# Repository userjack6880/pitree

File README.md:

There's not much to say. This is a perl script that enables a raspberry pi to control a specific
hardware tree, files should be included with this script. The schematics and board layout are 
distributed under Creative Commons Attribution-ShareAlike 4.0 International. The software is
distributed under GNU General Public License v3.

You'll need a few perl modules to get this working.

- DateTime
- JSON
- Device::BCM2835
- Switch
- Data::Dumper
- LWP::UserAgent
- LWP::Protocol::https
- Time::HiRes qw(usleep)
- Curses
- Net::Ping

Have a Merry Christmas and a Happy New Year.

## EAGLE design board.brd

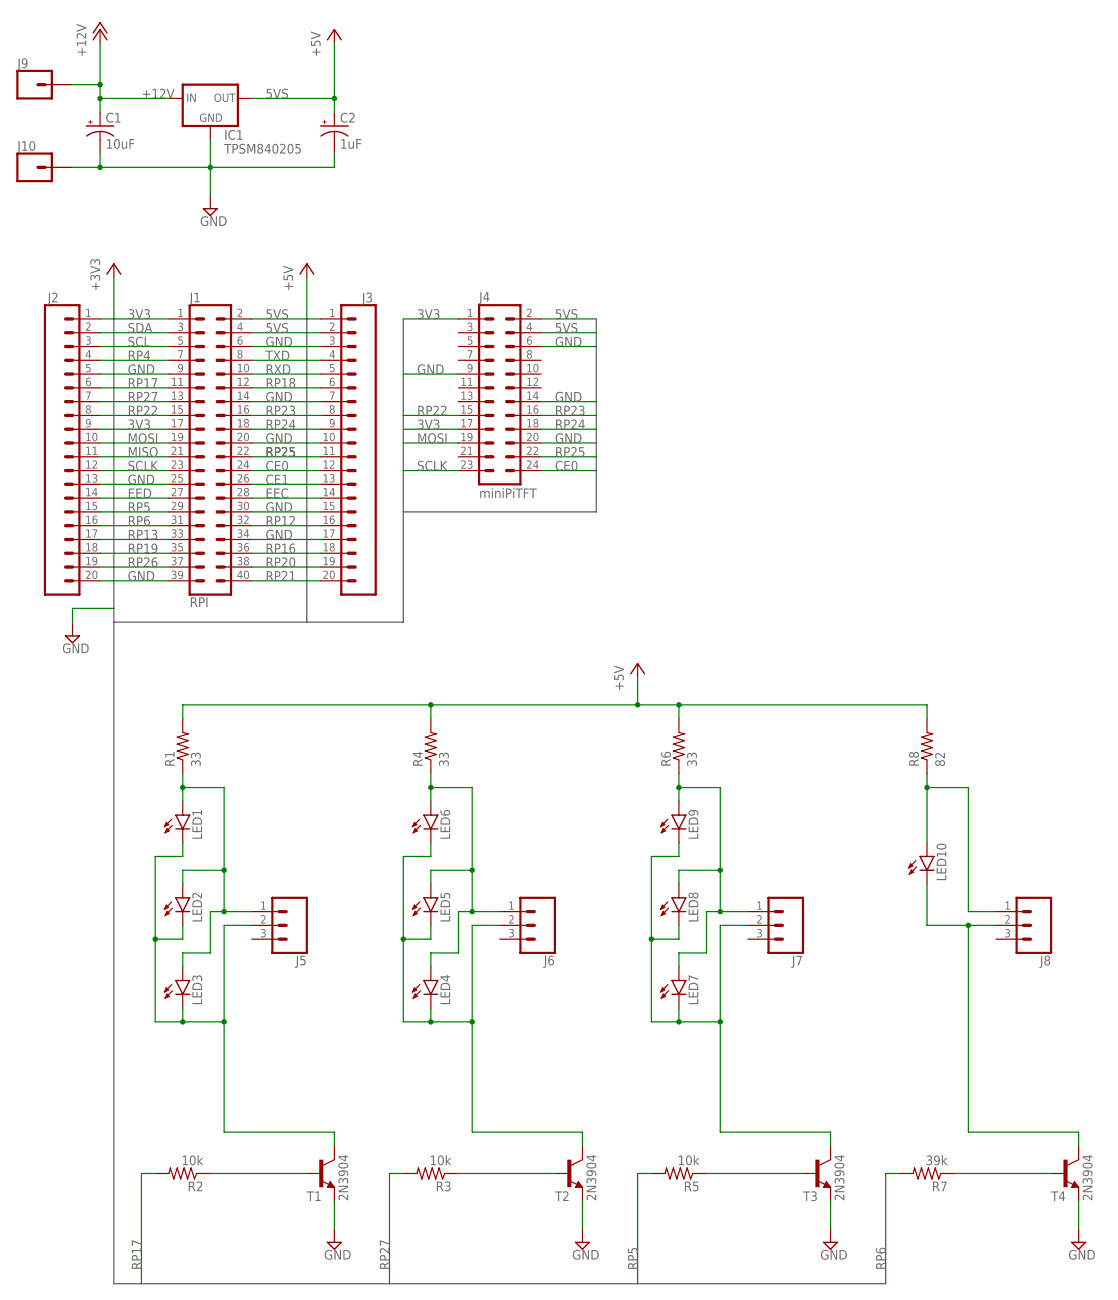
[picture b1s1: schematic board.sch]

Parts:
C1: 10uF; E2,5-6E
C2: 1uF; E2,5-6E
IC1: TPSM840205; 78XXS
J1: RPI; 2X20
J2, J3: CONN_20; 1X20
J4: miniPiTFT; 2X12
J5, J6, J7, J8: CONN_03; 1X03
J9, J10: CONN_01; 1X01
LED1, LED2, LED3, LED4, LED5, LED6, LED7, LED8, LED9, LED10: LED3MM
R1, R4, R6: 33; 0204/7
R2, R3, R5: 10k; 0204/7
R7: 39k; 0204/7
R8: 82; 0204/7
T1, T2, T3, T4: 2N3904; TO92

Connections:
3V3: J1.1, J1.17, J2.1, J2.9, J4.1, J4.17
5VS: C2.+, IC1.OUT, J1.2, J1.4, J3.1, J3.2, J4.2, J4.4, R1.2, R4.2, R6.2, R8.2
+12V: C1.+, IC1.IN, J9.1
CE0: J1.24, J3.12, J4.24
CE1: J1.26, J3.13
EEC: J1.28, J3.14
EED: J1.27, J2.14
GND: C1.-, C2.-, IC1.GND, J1.6, J1.9, J1.14, J1.20, J1.25, J1.30, J1.34, J1.39, J2.5, J2.13, J2.20, J3.3, J3.7, J3.10, J3.15, J3.17, J4.6, J4.9, J4.14, J4.20, J10.1, T1.3 (E), T2.3 (E), T3.3 (E), T4.3 (E)
MISO: J1.21, J2.11
MOSI: J1.19, J2.10, J4.19
unnamed: J5.1, LED1.A, LED2.A, LED3.A, R1.1
unnamed: J5.2, LED1.K (C), LED2.K (C), LED3.K (C), T1.1 (C)
unnamed: R2.1, T1.2 (B)
unnamed: J6.2, LED4.K (C), LED5.K (C), LED6.K (C), T2.1 (C)
unnamed: R3.1, T2.2 (B)
unnamed: J6.1, LED4.A, LED5.A, LED6.A, R4.1
unnamed: R5.1, T3.2 (B)
unnamed: R7.1, T4.2 (B)
unnamed: J7.1, LED7.A, LED8.A, LED9.A, R6.1
unnamed: J7.2, LED7.K (C), LED8.K (C), LED9.K (C), T3.1 (C)
unnamed: J8.1, LED10.A, R8.1
unnamed: J8.2, LED10.K (C), T4.1 (C)
RP4: J1.7, J2.4
RP5: J1.29, J2.15, R5.2
RP6: J1.31, J2.16, R7.2
RP12: J1.32, J3.16
RP13: J1.33, J2.17
RP16: J1.36, J3.18
RP17: J1.11, J2.6, R2.2
RP18: J1.12, J3.6
RP19: J1.35, J2.18
RP20: J1.38, J3.19
RP21: J1.40, J3.20
RP22: J1.15, J2.8, J4.15
RP23: J1.16, J3.8, J4.16
RP24: J1.18, J3.9, J4.18
RP25: J1.22, J3.11, J4.22
RP26: J1.37, J2.19
RP27: J1.13, J2.7, R3.2
RXD: J1.10, J3.5
SCL: J1.5, J2.3
SCLK: J1.23, J2.12, J4.23
SDA: J1.3, J2.2
TXD: J1.8, J3.4

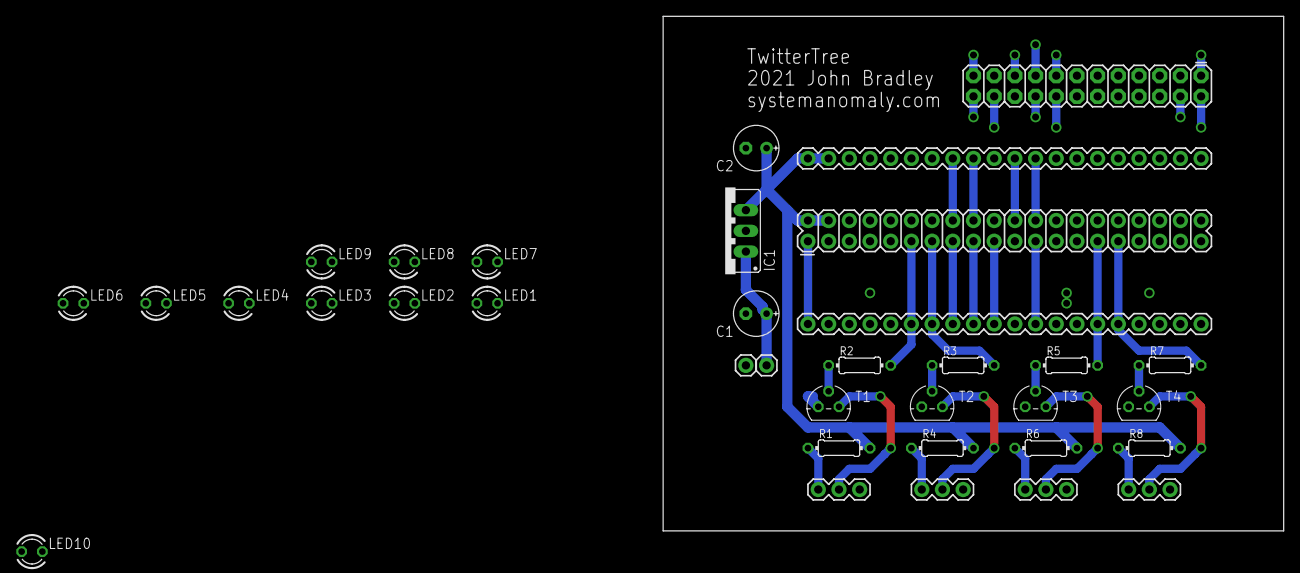
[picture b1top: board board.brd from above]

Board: 2 copper layers, 76.2 x 63.2 mm, 35 parts (0 on the bottom side), 44 nets.

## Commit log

2021-12-21 typo fix
2021-12-24 lol christmas
2022-07-27 Relicensed to MIT
    Mostly because this is silly code that I don't care who uses.

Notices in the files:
parts and their libraries:
SparkFun-Connectors: Licensing: Creative Commons ShareAlike 4.0 International - https://creativecommons.org/licenses/by-sa/4.0
